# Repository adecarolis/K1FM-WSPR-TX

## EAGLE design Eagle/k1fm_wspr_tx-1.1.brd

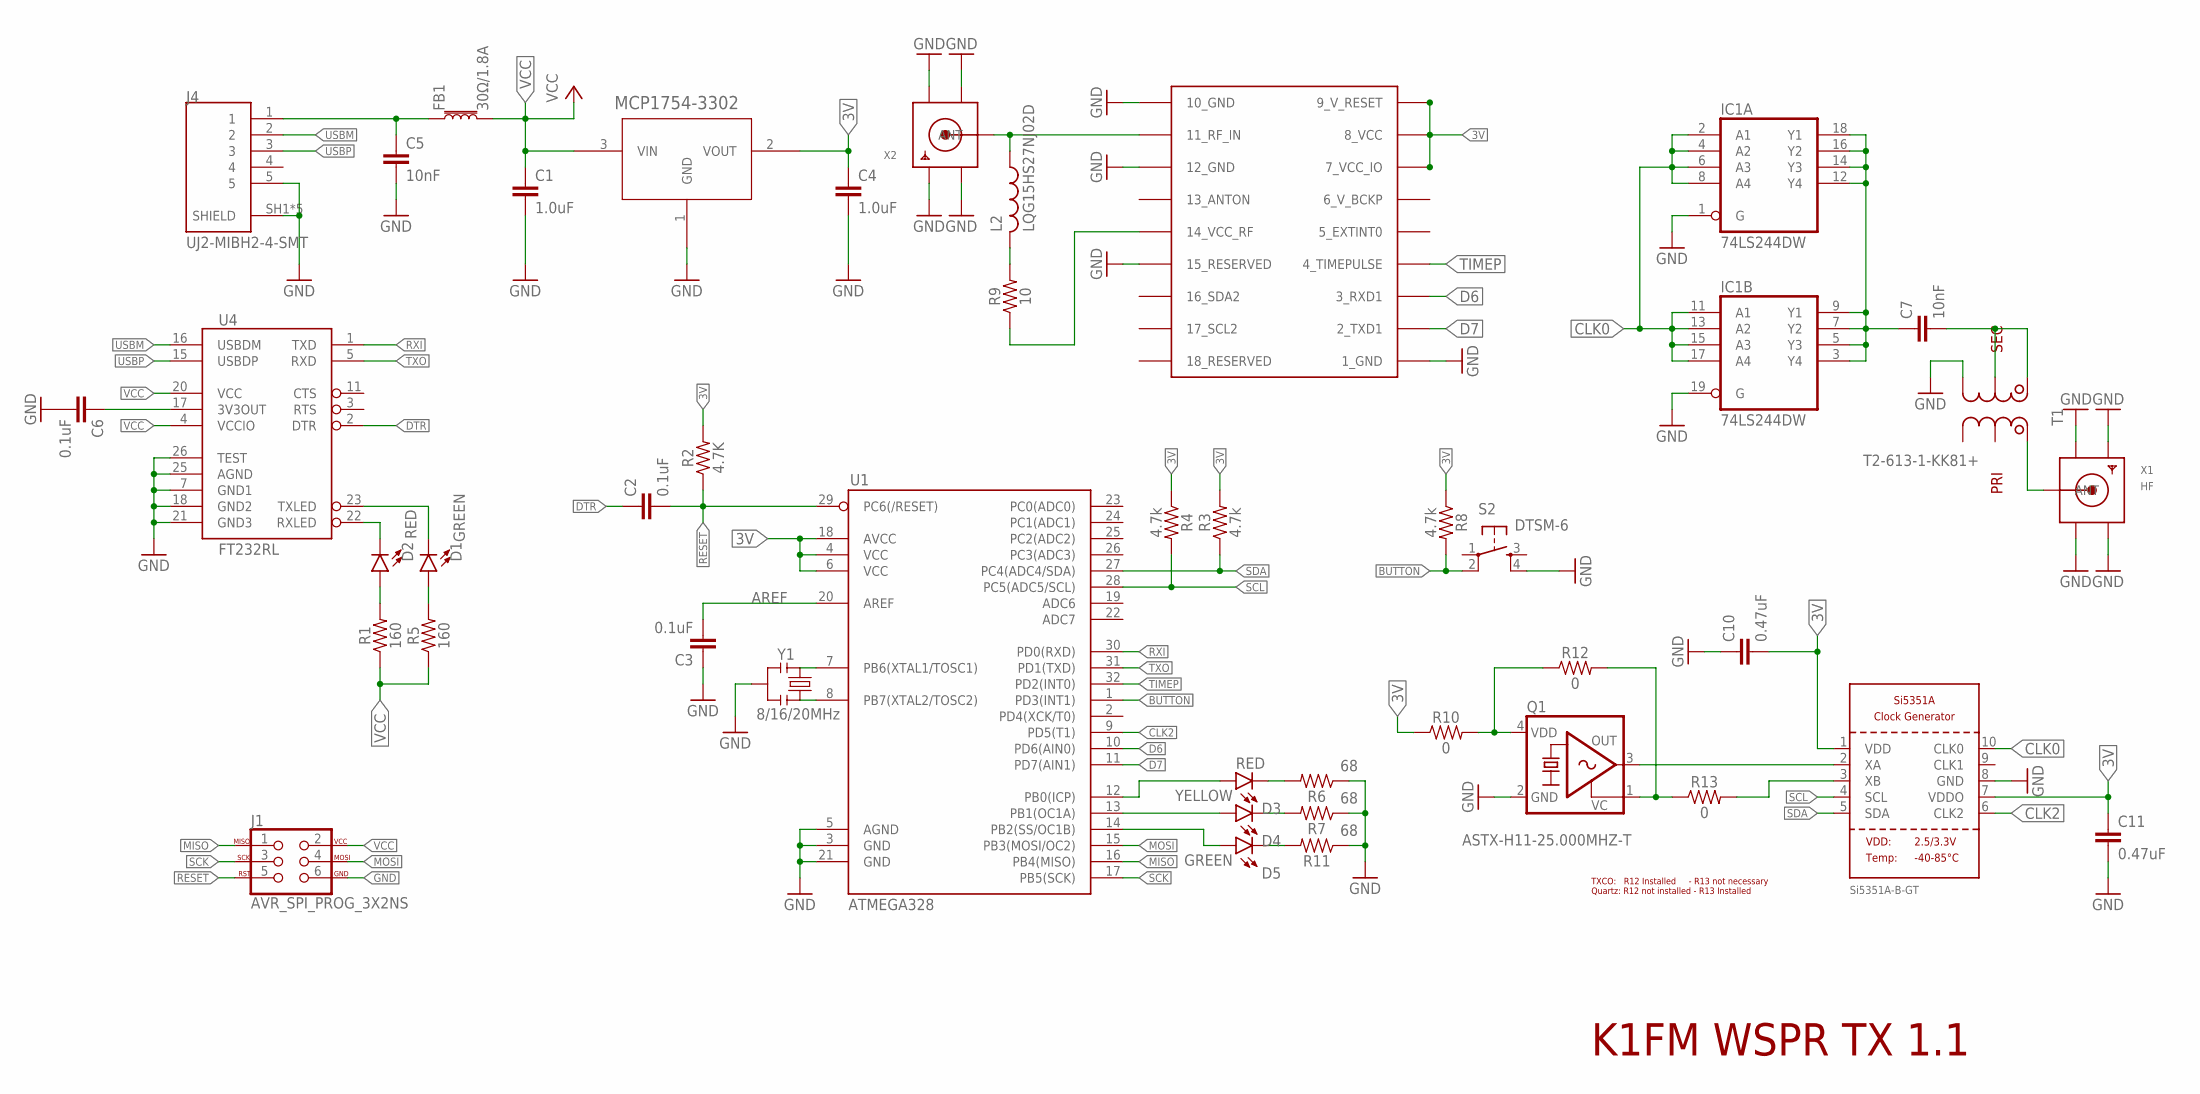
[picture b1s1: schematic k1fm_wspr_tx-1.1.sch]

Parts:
C1, C4: 1.0uF; 0603
C2, C3, C6: 0.1uF; 0603
C5, C7: 10nF; 0603
C10, C11: 0.47uF; 0603
D1, D5: GREEN; LED-0603
D2, D3: RED; LED-0603
D4: YELLOW; LED-0603
FB1: 30Ω/1.8A; 0603
GPS1: UBLOX_MAX
IC1: 74LS244DW; SO20W
J1: AVR_SPI_PROG_3X2NS; 2X3-NS
J4: UJ2-MIBH2-4-SMT; CUI_UJ2-MIBH2-4-SMT
L2: LQG15HS27NJ02D; RESC0402_M
Q1: ASTX-H11-25.000MHZ-T; 3.2X2.5_KXO-84
R1, R5: 160; 0603
R2: 4.7K; 0603
R3, R4, R8: 4.7k; 0603
R6, R7, R11: 68; 0603
R9: 10; 0603
R10, R12, R13: 0; 0603
S2: DTSM-6
T1: T2-613-1-KK81+; KK81
U1: ATMEGA328; TQFP32-08
U2: Si5351A-B-GT; MSOP10
U3: MCP1754X-XXXXX/C; SOT-23A_MC
U4: FT232RL; SSOP28DB
X1: HF; SMA_EDGELAUNCH
X2: SMACONNECTOR_EDGE; SMA_EDGELAUNCH
Y1: 8/16/20MHz; RESONATOR-SMD-1:1

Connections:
3V: C4.1, C10.2, C11.1, GPS1.7_VCC_IO, GPS1.8_VCC, GPS1.9_V_RESET, R2.2, R3.2, R4.1, R8.1, R10.1, U1.4 (VCC), U1.6 (VCC), U1.18 (AVCC), U2.1 (VDD), U2.7 (VDDO), U3.2 (VOUT)
AREF: C3.2, U1.20 (AREF)
BUTTON: R8.2, S2.2, U1.1 (PD3(INT1))
CLK0: IC1.2 (A1), IC1.4 (A2), IC1.6 (A3), IC1.8 (A4), IC1.11 (A1), IC1.13 (A2), IC1.15 (A3), IC1.17 (A4), U2.10 (CLK0)
CLK2: U1.9 (PD5(T1)), U2.6 (CLK2)
D6: GPS1.3_RXD1, U1.10 (PD6(AIN0))
D7: GPS1.2_TXD1, U1.11 (PD7(AIN1))
DTR: C2.1, U4.2 (DTR)
GND: C1.2, C3.1, C4.2, C5.2, C6.2, C10.1, C11.2, GPS1.1_GND, GPS1.10_GND, GPS1.12_GND, GPS1.15_RESERVED, IC1.1 (G), IC1.10 (GND), IC1.19 (G), J1.6, J4.5, J4.SH1 (SHIELD), J4.SH2 (SHIELD), J4.SH3 (SHIELD), J4.SH4 (SHIELD), J4.SH5 (SHIELD), Q1.2 (GND), R6.1, R7.1, R11.1, S2.4, T1.1 (S2), U1.3 (GND), U1.5 (AGND), U1.21 (GND), U2.8 (GND), U3.1 (GND), U4.7 (GND1), U4.18 (GND2), U4.21 (GND3), U4.25 (AGND), U4.26 (TEST), X1.GND@1 (GND4), X1.GND@2 (GND3), X1.GND@3 (GND2), X1.GND@4 (GND1), X2.GND@1 (GND4), X2.GND@2 (GND3), X2.GND@3 (GND2), X2.GND@4 (GND1), Y1.2
MISO: J1.1, U1.16 (PB4(MISO))
MOSI: J1.4, U1.15 (PB3(MOSI/OC2))
unnamed: GPS1.11_RF_IN, L2.1, X2.P (ANT)
unnamed: D2.C, U4.22 (RXLED)
unnamed: C7.1, IC1.3 (Y4), IC1.5 (Y3), IC1.7 (Y2), IC1.9 (Y1), IC1.12 (Y4), IC1.14 (Y3), IC1.16 (Y2), IC1.18 (Y1)
unnamed: T1.4 (P1), X1.P (ANT)
unnamed: C7.2, T1.2 (ST), T1.3 (S1)
unnamed: Q1.3 (OUT), U2.2 (XA)
unnamed: D1.C, U4.23 (TXLED)
unnamed: C5.1, FB1.1, J4.1
unnamed: D2.A, R1.2
unnamed: D1.A, R5.2
unnamed: D3.A, U1.12 (PB0(ICP))
unnamed: D4.A, U1.13 (PB1(OC1A))
unnamed: D3.C, R6.2
unnamed: C6.1, U4.17 (3V3OUT)
unnamed: D4.C, R7.2
unnamed: Q1.4 (VDD), R10.2, R12.1
unnamed: L2.2, R9.2
unnamed: GPS1.14_VCC_RF, R9.1
unnamed: D5.A, U1.14 (PB2(SS/OC1B))
unnamed: D5.C, R11.2
unnamed: R13.2, U2.3 (XB)
unnamed: Q1.1 (VC), R12.2, R13.1
unnamed: U1.8 (PB7(XTAL2/TOSC2)), Y1.3
unnamed: U1.7 (PB6(XTAL1/TOSC1)), Y1.1
RESET: C2.2, J1.5, R2.1, U1.29 (PC6(/RESET))
RXI: U1.30 (PD0(RXD)), U4.1 (TXD)
SCK: J1.3, U1.17 (PB5(SCK))
SCL: R4.2, U1.28 (PC5(ADC5/SCL)), U2.4 (SCL)
SDA: R3.1, U1.27 (PC4(ADC4/SDA)), U2.5 (SDA)
TIMEP: GPS1.4_TIMEPULSE, U1.32 (PD2(INT0))
TXO: U1.31 (PD1(TXD)), U4.5 (RXD)
USBM: J4.2, U4.16 (USBDM)
USBP: J4.3, U4.15 (USBDP)
VCC: C1.1, FB1.2, IC1.20 (VCC), J1.2, R1.1, R5.1, U3.3 (VIN), U4.4 (VCCIO), U4.20 (VCC)

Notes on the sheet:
K1FM WSPR TX 1.1
TXCO: R12 Installed - R13 not necessary Quartz: R12 not installed - R13 Installed

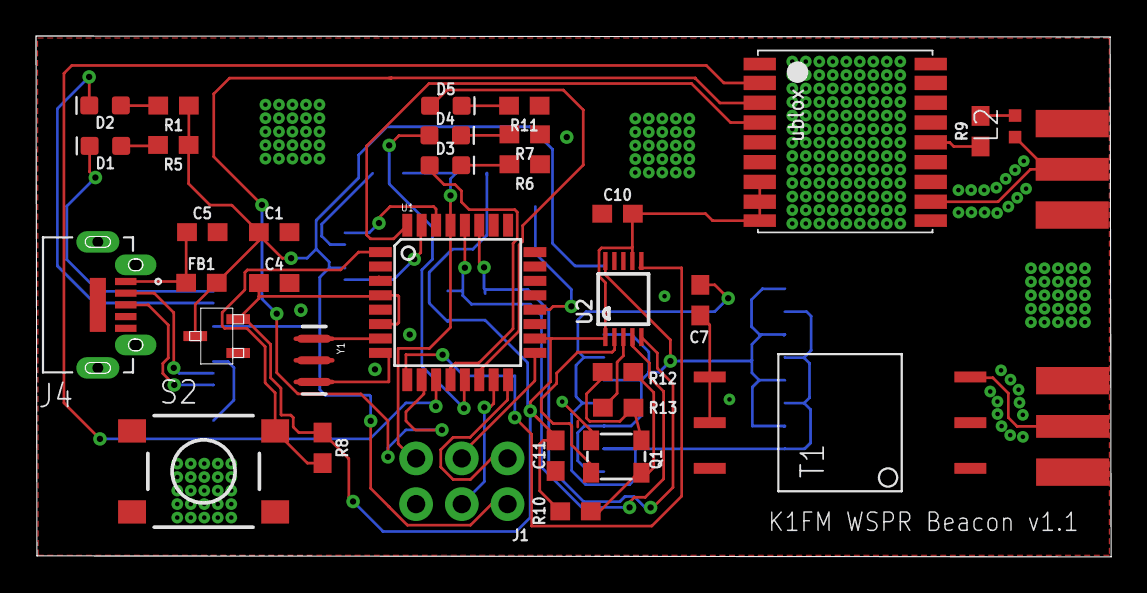
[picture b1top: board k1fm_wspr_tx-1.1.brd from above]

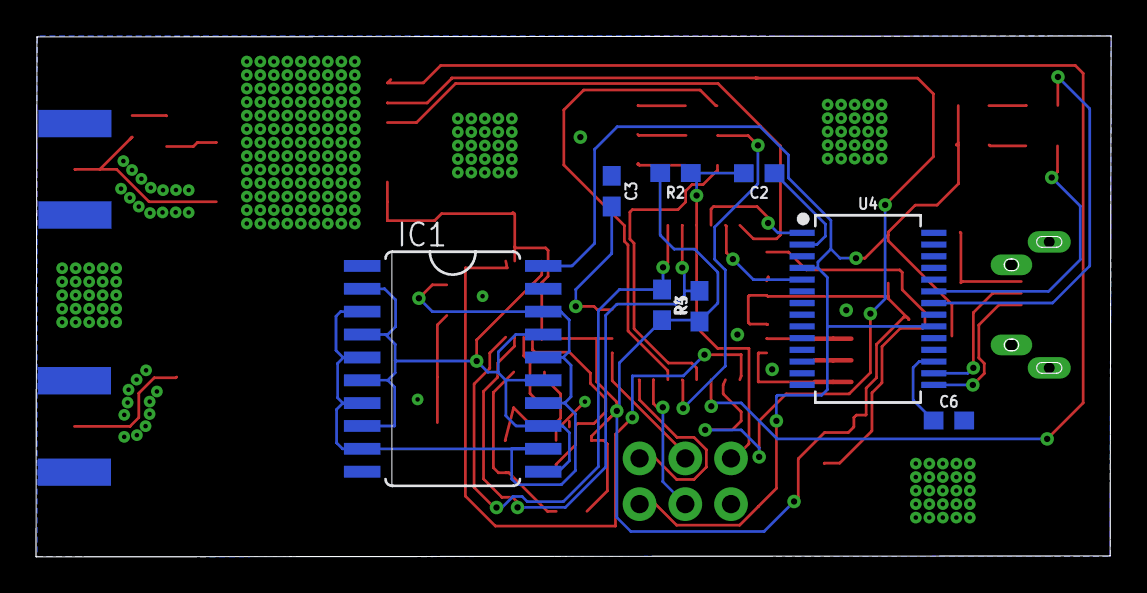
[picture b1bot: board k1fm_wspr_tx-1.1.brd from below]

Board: 2 copper layers, 59.7 x 28.9 mm, 43 parts (8 on the bottom side), 45 nets.

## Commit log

2019-07-13 First working version
2019-07-13 Add gitignore
2019-07-13 Add board v1.0
2019-07-13 Add board v1.1
2019-07-13 Added multiple bands, various features
2019-07-13 Bugfixes
2019-07-14 Add copyright notice
2019-07-14 Add comments

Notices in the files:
parts and their libraries:
SparkFun-Capacitors: Licensing: Creative Commons ShareAlike 4.0 International - https://creativecommons.org/licenses/by-sa/4.0
microbuilder: This work is placed in the public domain, and may be freely used for commercial and non-commercial work with the following conditions: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
